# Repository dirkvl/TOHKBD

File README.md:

# TOHKBD rev2

## History

When Jolla announced their [Jolla phone](https://www.youtube.com/watch?v=tRZxM9rNyZ4) the mobile Linux community rejoiced and finally had a place to go from their N8x, N900, N950 or N9. Together with the new operating system on the inside, the OtherHalf concept was introduced. With direct data-connection into the phone it is now possible to extend the functionality on a hardware level.

Naturally, a keyboard OtherHalf was the [most requested feature](http://www.jollatides.com/2013/10/03/other-half-lets-prioritise/) by the community by far. Jolla however was still getting started and getting their phone launched with the minimum of Sailors at the time. This was left to the community to develop.

In [June 2013](http://talk.maemo.org/showthread.php?t=91535) one idiot thought he could easily make this -how hard could it be, really?- and started on his journey. After some time this foolish individual make TOHKBD-rev1: hackish, ugly, frankensteined, terrible durability and way too much work to assemble. But it worked. 

After this project ended there was a period of other Funky-TOH development, with during that time a lot of requests of making more keyboards. Little did they knew that in the background the imfamous 'dirkvl' together with his trusty 'kimmoli' were cooking up a new version. A better one. The One.

With an [open application](https://twitter.com/andrewzhilin/status/493485714798313472) on the hashweb/tweetspace Andrew joined the team and provid himself to be the missing piece of the three piece puzzle. With a complete team, a solid design and a strong backing from the rest of the community, the TOHKBD-team set out onto the open crowdfunding sea. [And struck gold.](https://www.kickstarter.com/projects/2028347278/tohkbd-the-other-half-keyboard-for-your-jolla)

## Hardware

### Electronics

#### TOH-cover

In the cover that snap onto the phone there is very little going on. There is a PCB that connects to all [6 pogo-pins](https://jolla.com/the-other-half-developer-kit/). Connecting to these pins is a [voltage regulator](https://github.com/dirkvl/TOHKBD/tree/master/Eagle/pics/MCP1703.jpg) and an EEPROM. 

This is a memory module that contains a [Vendor and Product ID](https://wiki.merproject.org/wiki/The_other_half). The phone reads this EEPROM when it connects to start the appropriate driver.

If the driver is not installed, the phone reads the [NFC tag](http://www.nfcnetstore.com/SMARTRAC+Midas+NTAG203+12x19+mm+clear+%28NFC+Forum+Type+2%29/p/121/) on the PCB and pulls the driver from the store.

With two contact pads (8mm PCBs) the keyboard piece can make contact, all 6 pins are available.

#### Keyboard piece

In the keyboard a little more is going on. The main driver is the [TCA8424](http://www.ti.com/product/TCA8424/description). It runs on 1.8V I2C lines and has three notification LEDs connected, where the TCA8424 acts as an open drain. The LEDs have some probing pads for testing during production.

This connects to the keyboard matrix. It waits untill a key is pressed, then starts scanning and notifies the phone via the INT pin that is has data to be read.

There is an additional EEMPROM in the keyboard piece, containing the keypad layout version. The A0 address pin is pulled high to make it shift one address place and not conflict with the EEPROM in the TOH-cover.

The backlight consists of 10 x 0402 LEDs, controlled with a [n-channel MOSFET](http://en.wikipedia.org/wiki/MOSFET) by the TCA8424.

The keyboard detection is done with a PNP transistor.

```
1. Phone detects TOH-cover
2. Phone launches TOHKBD driver
3. The driver shuts down the 3V3 line and starts listening to the interrupt
4. When the keyboard connects, the PNP transistor shorts the interrupt line to ground
5. The phone detects the grounding of INT and powers up de 3V3 line
6. The 3V3 disables the grounding on INT in the transistor
7. The phone probes whether the TCA8424 is present
8a. If the TCA8424 is present, the keyboard is present and working and all is set in motion
8b. If the TCA8424 is not present, something is wrong and the phone goes back to step 3
```

SMD part list:
```
TCA8424 - QFN40
CAT24C02 - DFN6
IRLML5203 - SOT-3
10K pullup/downs - 0603
10R led resistors - 0603
MCP1700 - SOT-3
0.1uF 6V capacitors - 0603
3.15V highbright leds - 0402
Pogo pins - Mill-Max 0906-0-15-20-76-14-11-0 (Mouser P/N: 575-906015)
```

### PCBs

Made in Eagle Cadsoft. The gerber files are linked below:

[Cover PCB](https://raw.githubusercontent.com/dirkvl/TOHKBD/master/Eagle/Cover.rar)

[Keyboard PCB](https://raw.githubusercontent.com/dirkvl/TOHKBD/master/Eagle/Keyboard.rar)

### SMD assembly

The first step in SMD assembly is applying solder past on the PCB with a stencil printer.

Next a pick&place machine puts the components in the right place on the PCB. I use a TM220A.

Because the accuracy of the machine it not astronomical, the allignment of every component is checked and adjusted by hand if neccessary. 

The solderpaste is melted in a reflow oven. (T-962A)

Lastly the PCB is tested manually and all shorts are corrected with a soldering iron.

### Frames

The frames are 3D printed (using a process called lasersintering) by Shapeways. If you want to change the colour of your TOHKBD, you can order one of these parts from them:

Cover link
Keyboard link

### Magnet system

The keyboard part uses magnets to attach and detach in all positions. 

The magnets used are the [D61-N52](https://www.kjmagnetics.com/proddetail.asp?prod=D61-N52) and [D62-N52](https://www.kjmagnetics.com/proddetail.asp?prod=D62-N52) from KJMagnetics.

<insert picture with dimensions>

### Keypad

Credits to Andrew

### Layouts

designs, files etc

### Backplate

<Dimensions>

## Software

[Link to Kimmoli's Github](https://github.com/kimmoli/)

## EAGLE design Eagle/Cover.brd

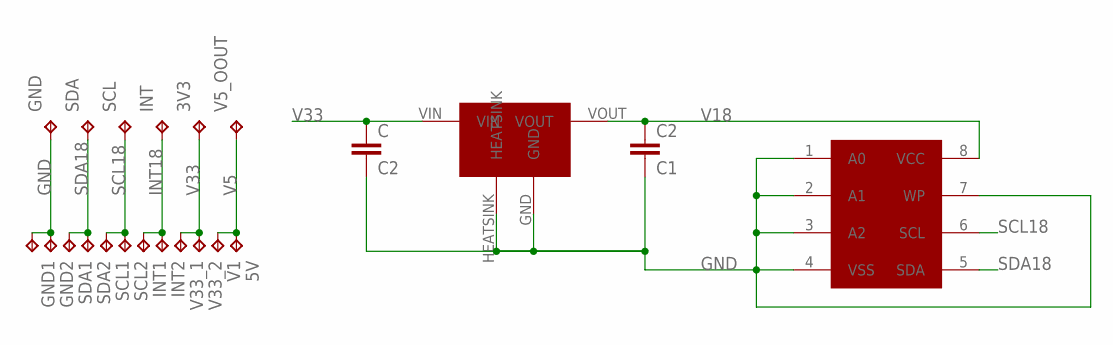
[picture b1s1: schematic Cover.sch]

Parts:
3V3: TPTP20SQ; TP20SQ
5V: V5; TP20SQ
C: C2; C0603
C2: C1; C0603
GND, GND1, GND2: TPTP20SQ; TP20SQ
INT, INT1, INT2: TPTP20SQ; TP20SQ
SCL, SCL1, SCL2: TPTP20SQ; TP20SQ
SDA: TPTP20SQ; TP20SQ
SDA1, SDA2: SDA; TP20SQ
U$1: CAT24
U$2: MCP1700-DFN6; DFN6-2X2
V1: V5; TP20SQ
V5_OOUT, V33_1, V33_2: TPTP20SQ; TP20SQ

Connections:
GND: C.2, C2.2, GND.TP, GND1.TP, GND2.TP, U$1.1 (A0), U$1.2 (A1), U$1.3 (A2), U$1.4 (VSS), U$1.7 (WP), U$2.GND, U$2.HEATSINK
INT18: INT.TP, INT1.TP, INT2.TP
SCL18: SCL.TP, SCL1.TP, SCL2.TP, U$1.6 (SCL)
SDA18: SDA.TP, SDA1.TP, SDA2.TP, U$1.5 (SDA)
V5: 5V.TP, V1.TP, V5_OOUT.TP
V18: C2.1, U$1.8 (VCC), U$2.VOUT
V33: 3V3.TP, C.1, U$2.VIN, V33_1.TP, V33_2.TP

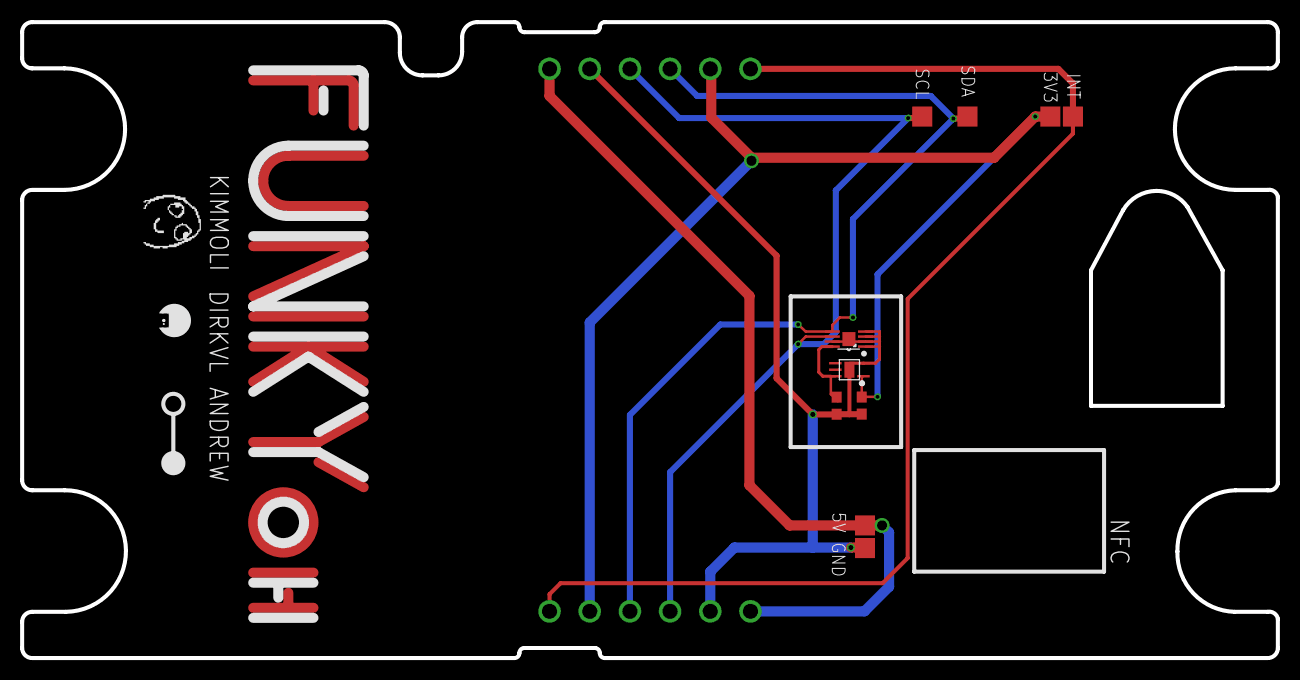
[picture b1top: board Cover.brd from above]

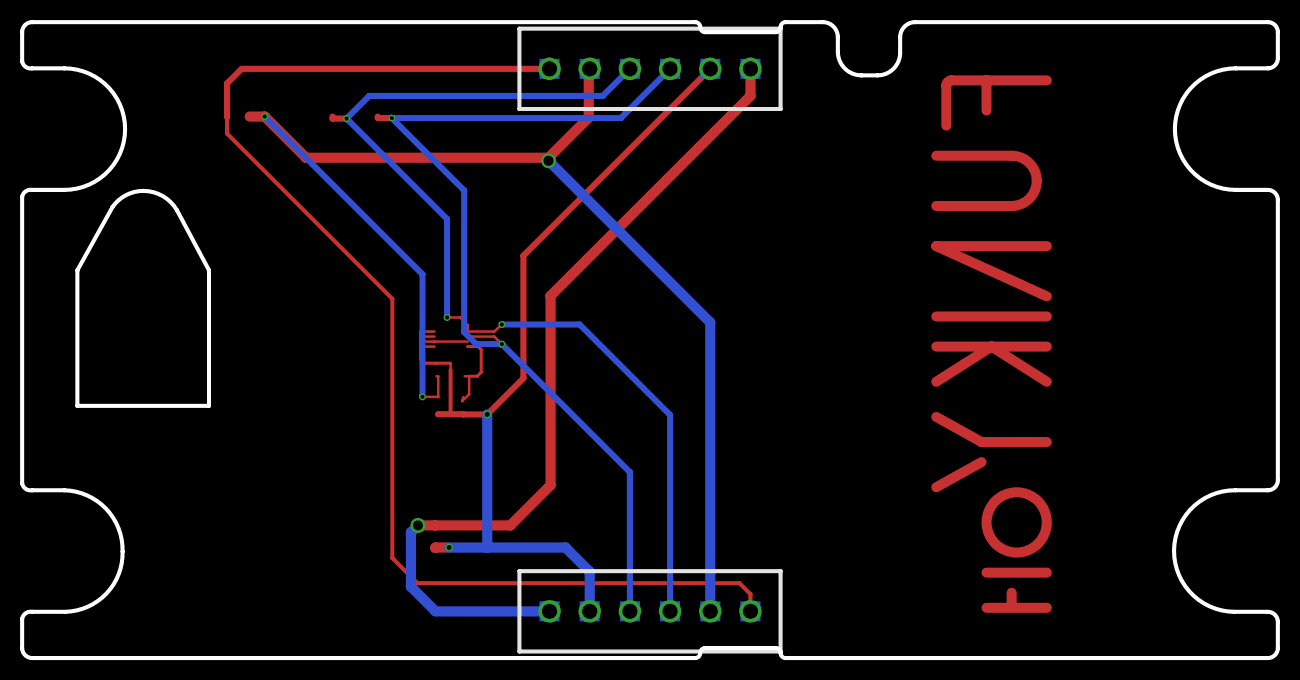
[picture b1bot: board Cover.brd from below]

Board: 2 copper layers, 125.0 x 63.3 mm, 24 parts (12 on the bottom side), 7 nets.

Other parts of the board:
U$3: FUNKY
U$4: DAFUG

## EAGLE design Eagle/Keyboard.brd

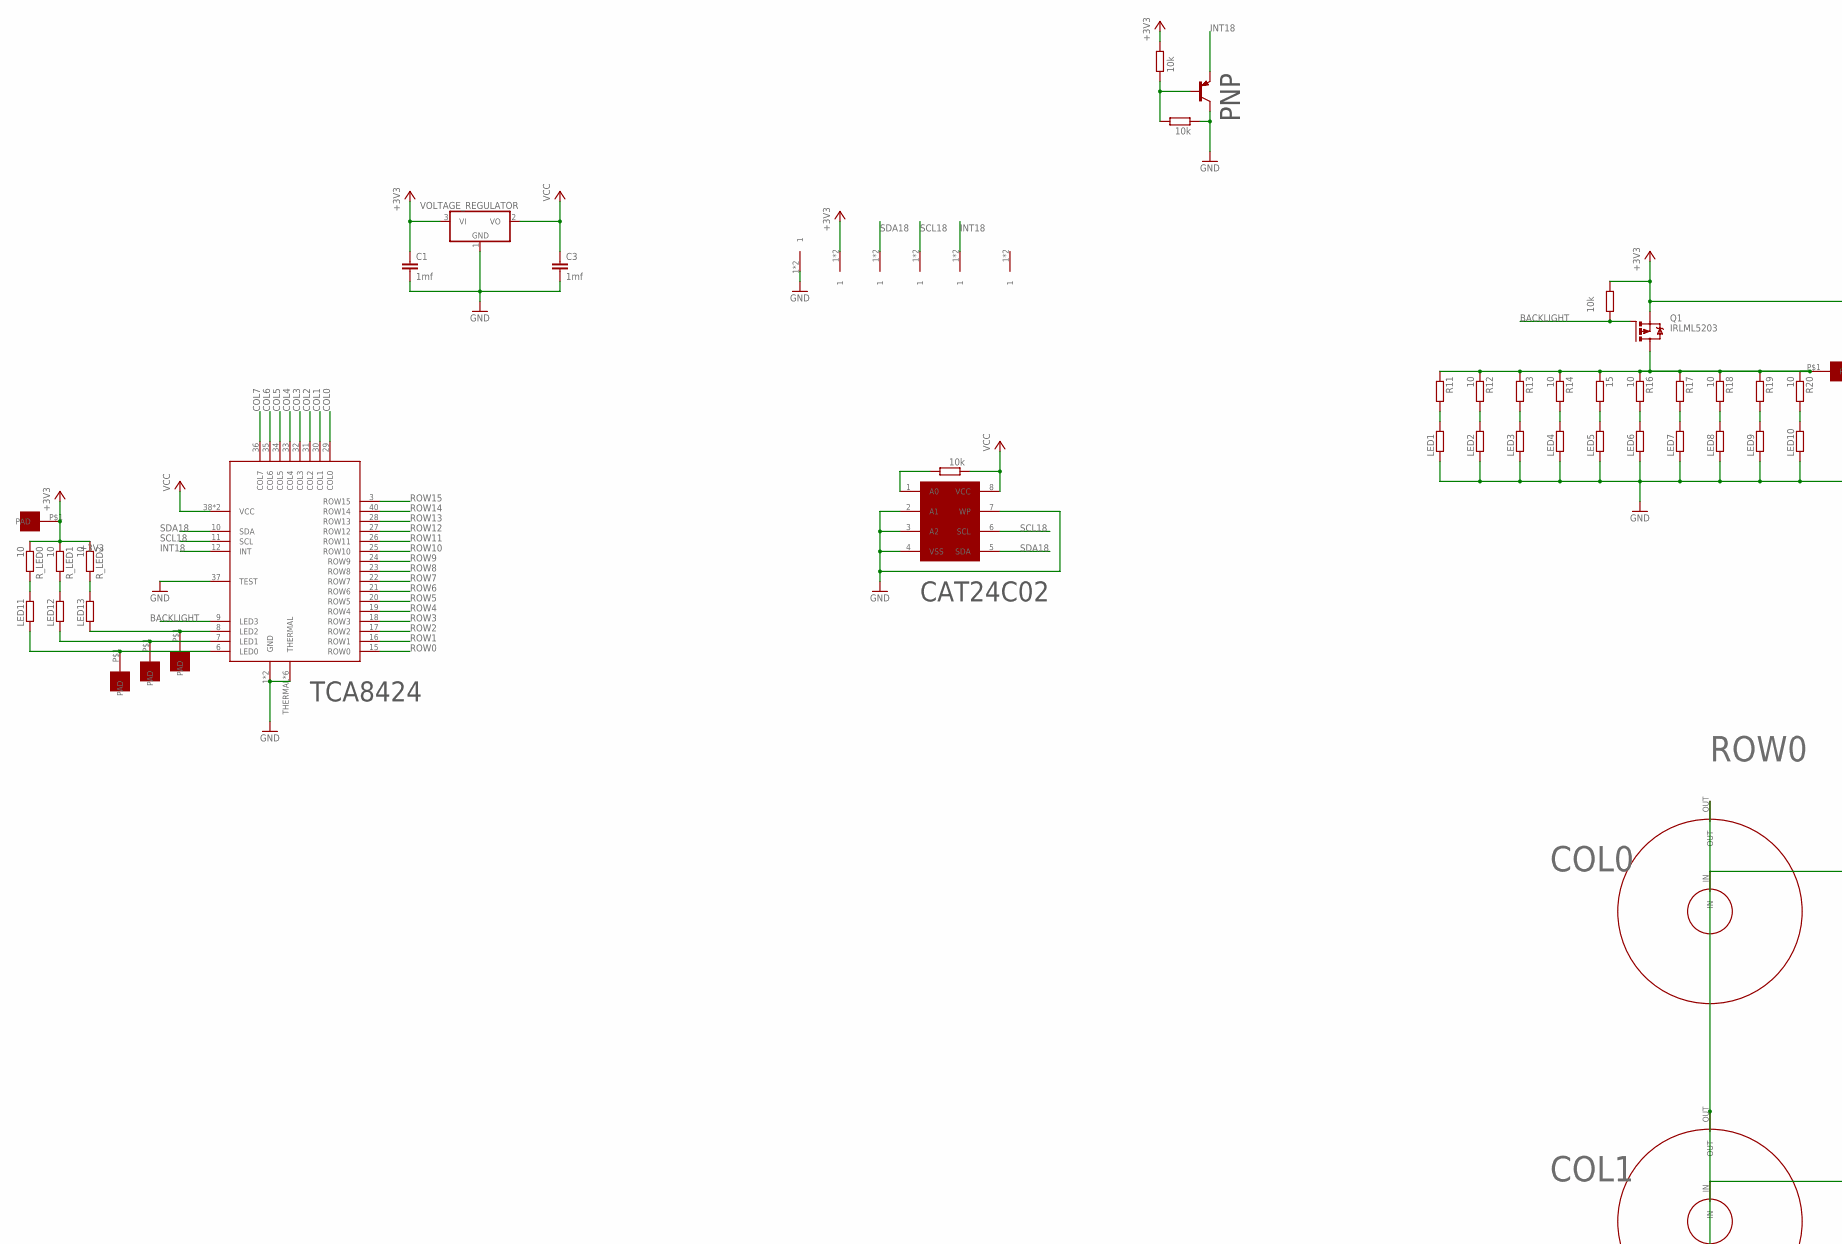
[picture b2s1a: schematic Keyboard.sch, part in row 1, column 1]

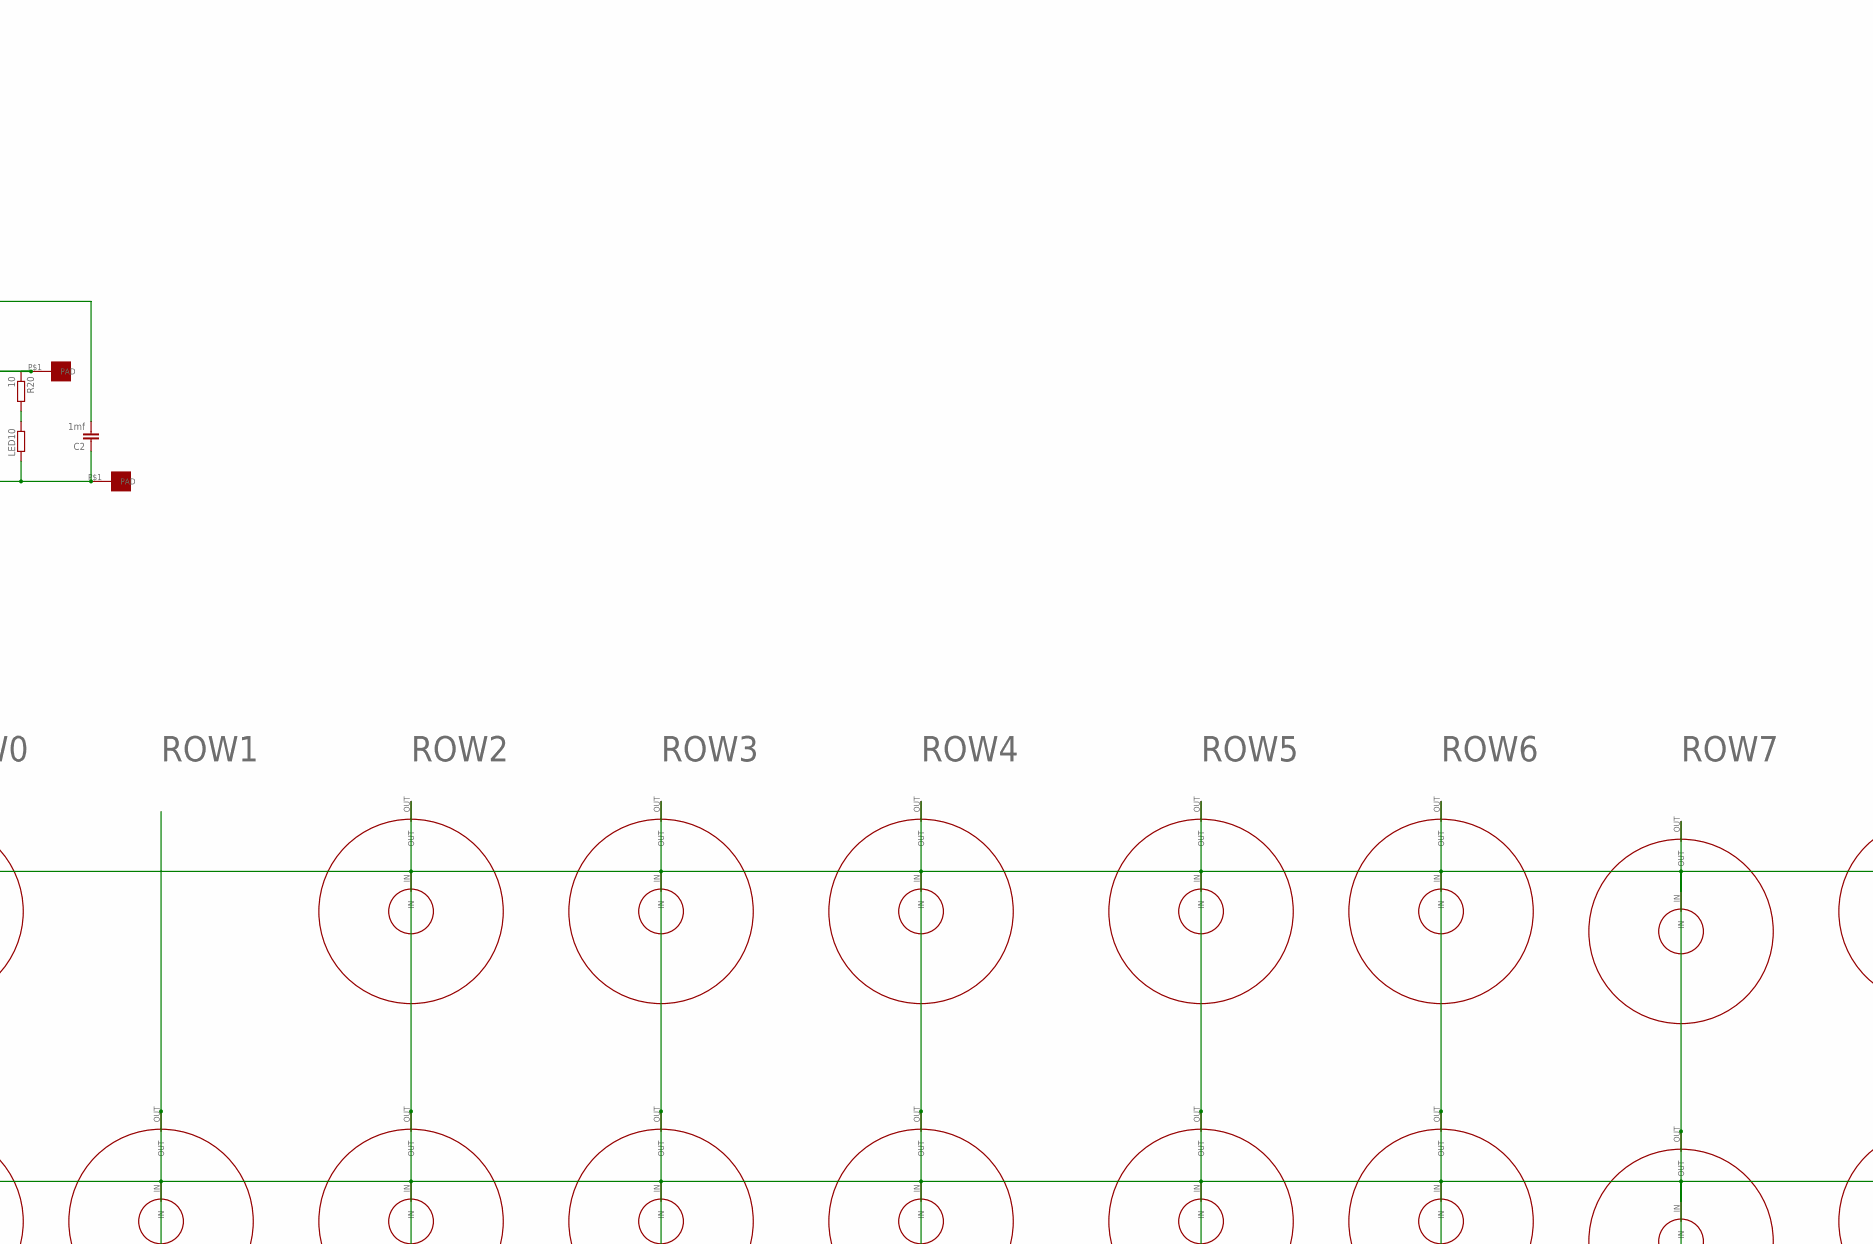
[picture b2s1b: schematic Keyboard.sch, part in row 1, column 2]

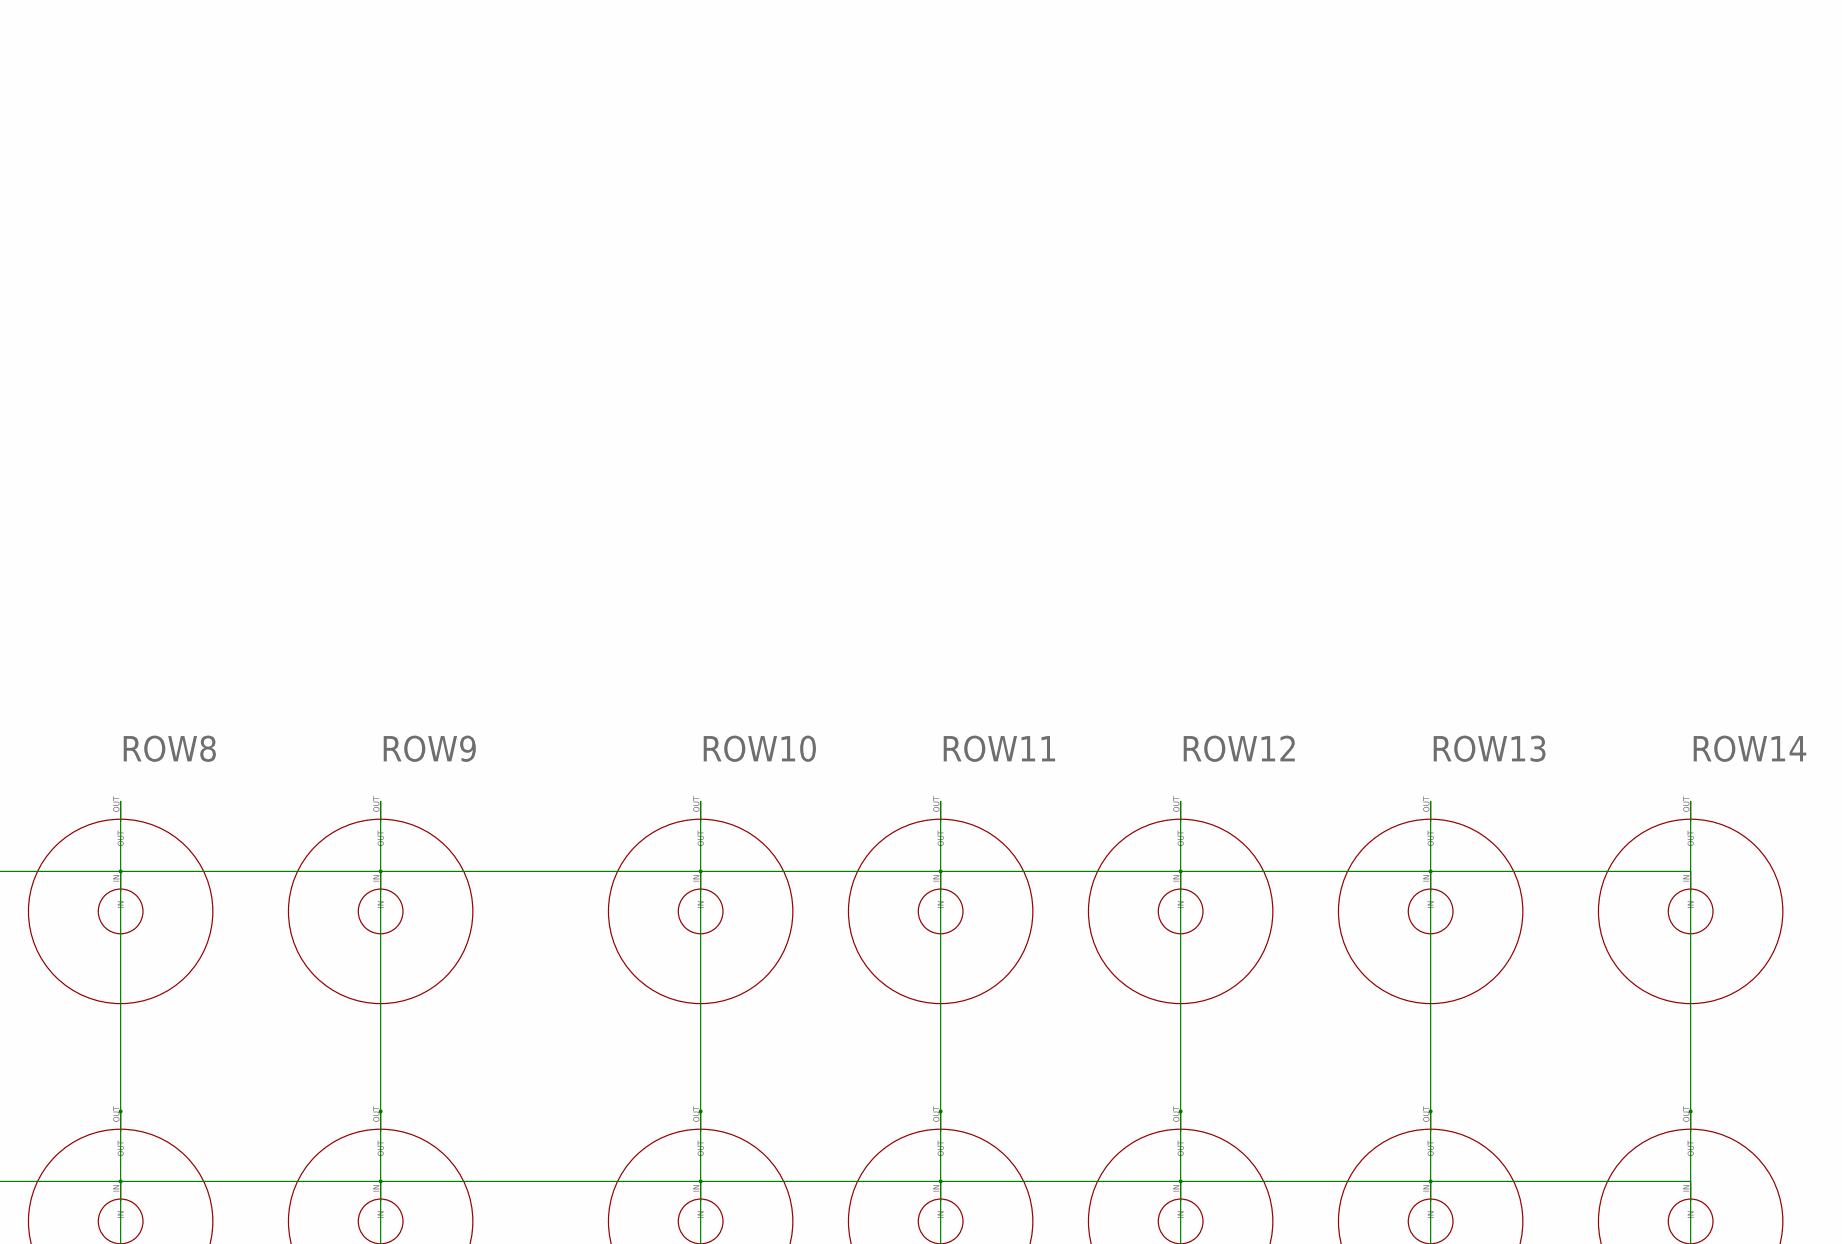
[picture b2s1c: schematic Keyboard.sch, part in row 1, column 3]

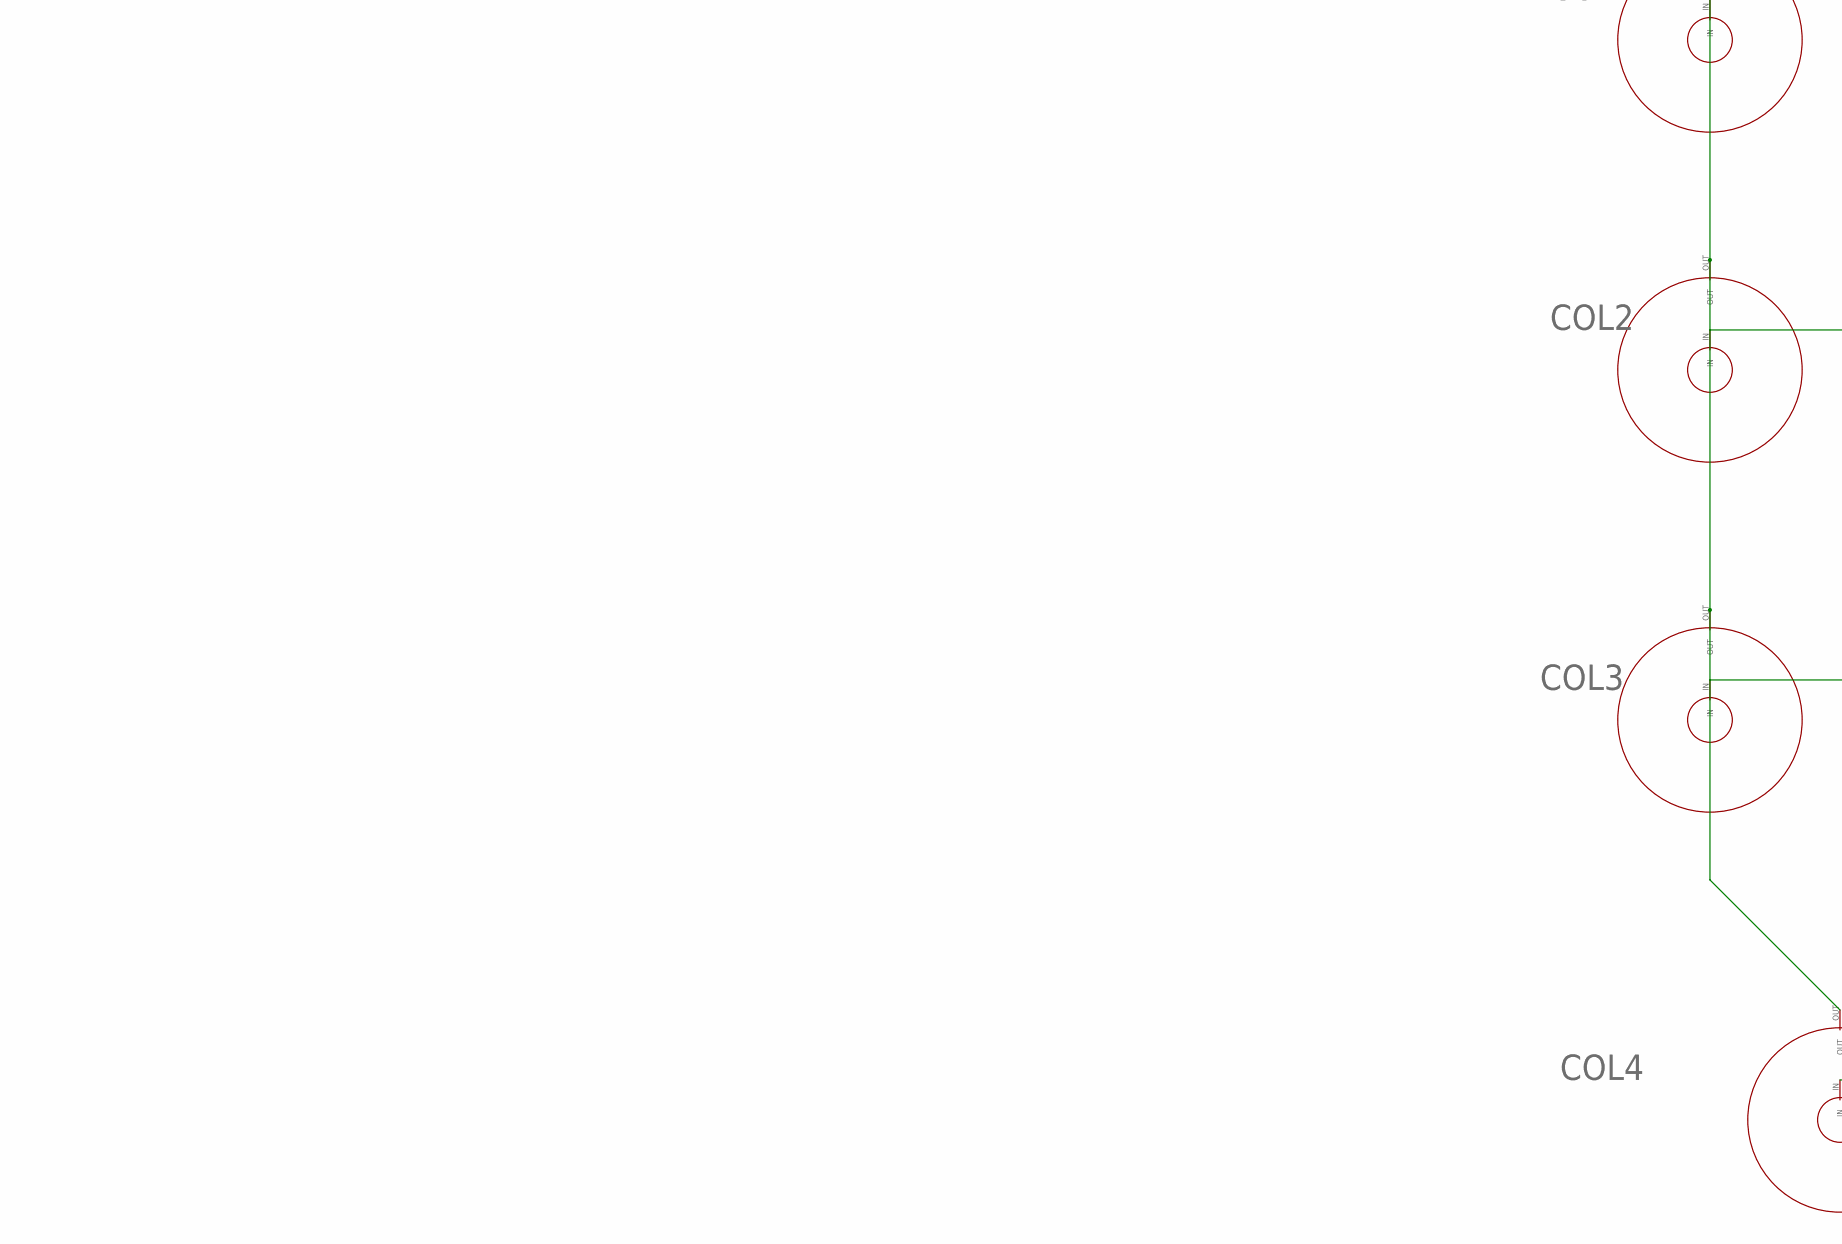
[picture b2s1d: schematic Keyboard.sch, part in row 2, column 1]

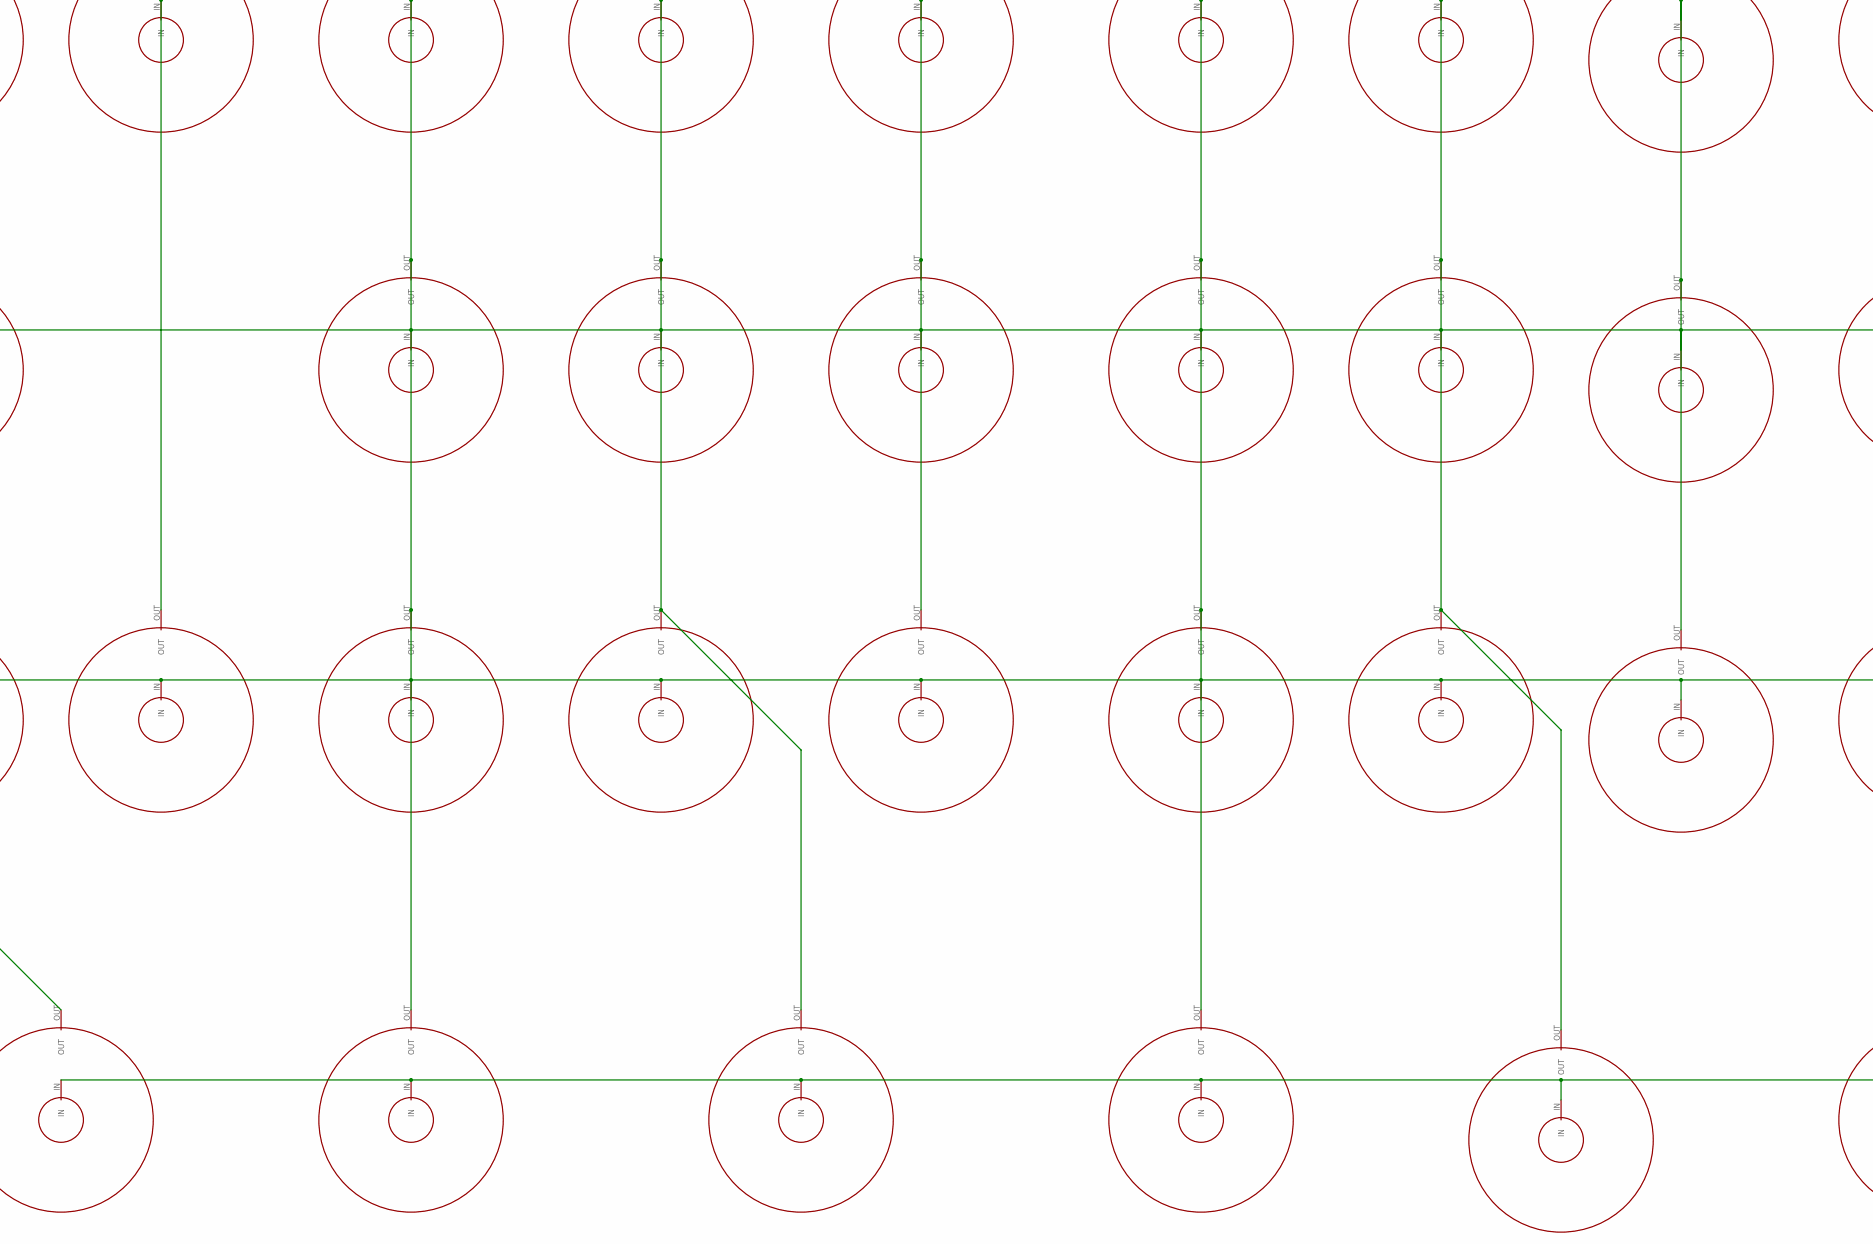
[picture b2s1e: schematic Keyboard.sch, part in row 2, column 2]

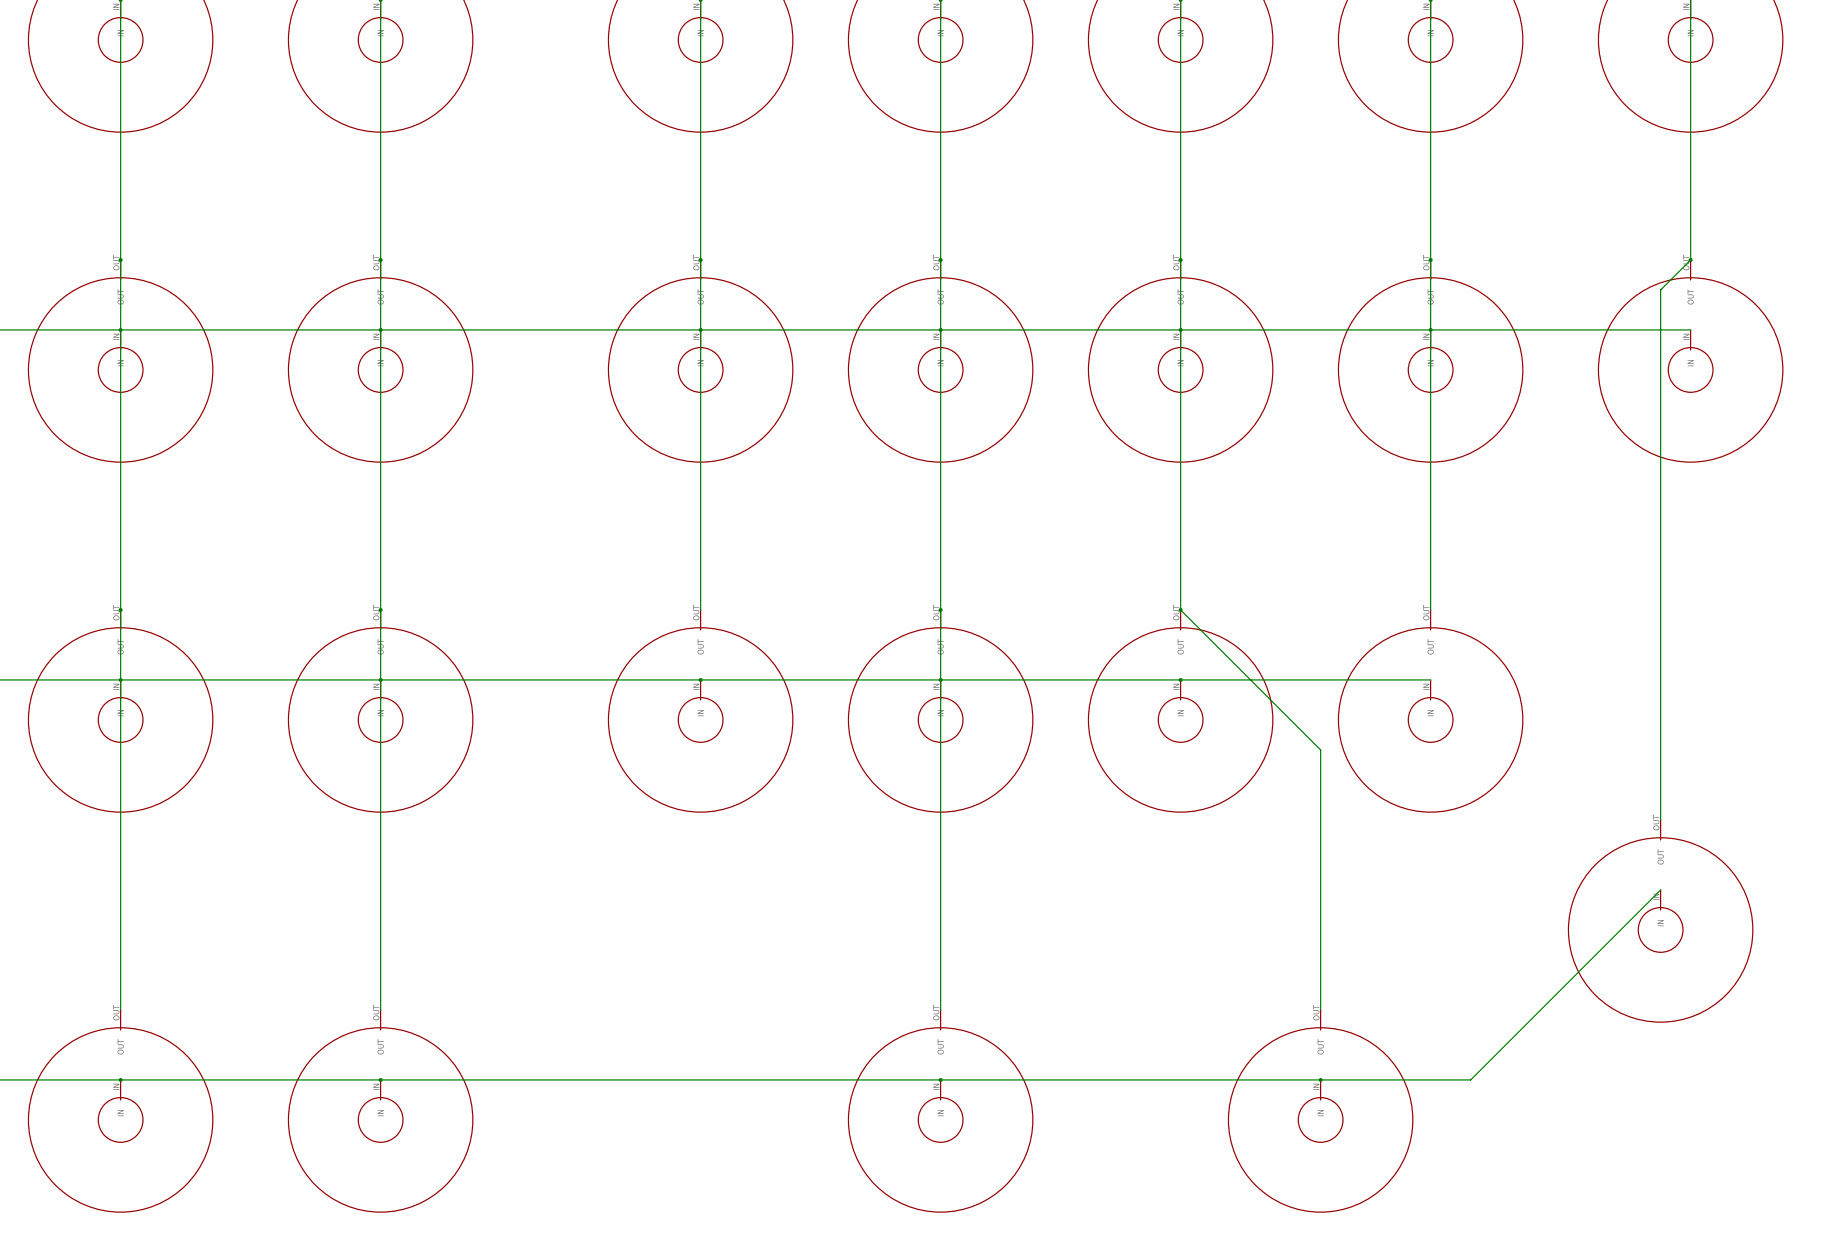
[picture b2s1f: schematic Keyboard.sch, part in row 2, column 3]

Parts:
15: R-EU_R0603; R0603
+: PAD
BL_PULLUP: 10k; R0603
C1, C2, C3: 1mf; C0603
LED1, LED2, LED3, LED4, LED5, LED6, LED7, LED8, LED9, LED10, LED11, LED12, LED13: R-EU_R0402; R0402
PNP_DOWN, PNP_DOWN1: 10k; R0603
PNP_UP: 10k; R0603
Q1: IRLML5203; MICRO3
Q2: MMBTA56-SOT23; SOT23
R11, R13, R17, R19: R-EU_R0603; R0603
R12, R14, R16, R18, R20: 10; R0603
R_LED0, R_LED1, R_LED2: 10; R0603
U$1: CAT24
U$2: TCA8424; QFN40
U$3, U$4, U$5, U$6, U$7, U$8: BOTTOM_POGO; POGO
U$9, U$11, U$12, U$13, U$14, U$15, U$16, U$17, U$18, U$19, U$20, U$21, U$22, U$23, U$24, U$25, U$26, U$27, U$28, U$29, U$30, U$31, U$32, U$33, U$34, U$35, U$36, U$37, U$38, U$39, U$40, U$41, U$42, U$43, U$44, U$45, U$46, U$47, U$48, U$49, U$50, U$51, U$52, U$54, U$55, U$56, U$57, U$58, U$59, U$60, U$61, U$62, U$63, U$64, U$65, U$66, U$67, U$68, U$69, U$70, U$72, U$73, U$75, U$76, U$77, U$79, U$81: DOME; 4MM
U$53, U$71, U$74, U$78, U$80: PAD
VOLTAGE_REGULATOR: SOT23

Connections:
+3V3: +.P$1, BL_PULLUP.1, C1.1, C2.2, PNP_UP.1, Q1.2 (S), R_LED0.1, R_LED1.1, R_LED2.1, U$4.1, U$4.P$2, VOLTAGE_REGULATOR.3 (VI)
BACKLIGHT: BL_PULLUP.2, Q1.1 (G), U$2.9 (LED3)
COL0: U$2.29 (COL0), U$9.IN, U$11.IN, U$12.IN, U$13.IN, U$14.IN, U$15.IN, U$16.IN, U$17.IN, U$18.IN, U$19.IN, U$20.IN, U$21.IN, U$22.IN, U$23.IN
COL1: U$2.30 (COL1), U$24.IN, U$25.IN, U$26.IN, U$27.IN, U$28.IN, U$29.IN, U$30.IN, U$31.IN, U$32.IN, U$33.IN, U$34.IN, U$35.IN, U$36.IN, U$37.IN, U$38.IN
COL2: U$2.31 (COL2), U$39.IN, U$40.IN, U$41.IN, U$42.IN, U$43.IN, U$44.IN, U$45.IN, U$46.IN, U$47.IN, U$48.IN, U$49.IN, U$50.IN, U$51.IN, U$52.IN
COL3: U$2.32 (COL3), U$54.IN, U$55.IN, U$56.IN, U$57.IN, U$58.IN, U$59.IN, U$60.IN, U$61.IN, U$62.IN, U$63.IN, U$64.IN, U$65.IN, U$66.IN, U$68.IN
COL4: U$2.33 (COL4), U$67.IN, U$69.IN, U$70.IN, U$72.IN, U$73.IN, U$75.IN, U$76.IN, U$77.IN, U$79.IN, U$81.IN
COL5: U$2.34 (COL5)
COL6: U$2.35 (COL6)
COL7: U$2.36 (COL7)
DRAIN: 15.1, Q1.3 (D), R11.1, R12.1, R13.1, R14.1, R16.1, R17.1, R18.1, R19.1, R20.1, U$78.P$1
GND: C1.2, C2.1, C3.2, LED1.1, LED2.1, LED3.1, LED4.1, LED5.1, LED6.1, LED7.1, LED8.1, LED9.1, LED10.1, PNP_DOWN.2, Q2.3 (C), U$1.2 (A1), U$1.3 (A2), U$1.4 (VSS), U$1.7 (WP), U$2.1 (GND), U$2.4 (GND), U$2.37 (TEST), U$2.THERMAL, U$2.VIA1 (THERMAL), U$2.VIA2 (THERMAL), U$2.VIA3 (THERMAL), U$2.VIA4 (THERMAL), U$2.VIA5 (THERMAL), U$3.1, U$3.P$2, U$80.P$1, VOLTAGE_REGULATOR.1 (GND)
INT18: Q2.2 (E), U$2.12 (INT), U$7.1, U$7.P$2
LED_GROUND0: LED11.2, R_LED0.2
LED_GROUND1: LED12.2, R_LED1.2
LED_GROUND2: LED13.2, R_LED2.2
unnamed: LED1.2, R11.2
unnamed: LED2.2, R12.2
unnamed: LED3.2, R13.2
unnamed: LED4.2, R14.2
unnamed: 15.2, LED5.2
unnamed: LED6.2, R16.2
unnamed: LED7.2, R17.2
unnamed: LED8.2, R18.2
unnamed: LED9.2, R19.2
unnamed: LED10.2, R20.2
unnamed: PNP_DOWN.1, PNP_UP.2, Q2.1 (B)
unnamed: LED12.1, U$2.7 (LED1), U$71.P$1
unnamed: LED11.1, U$2.6 (LED0), U$53.P$1
unnamed: LED13.1, U$2.8 (LED2), U$74.P$1
unnamed: PNP_DOWN1.2, U$1.1 (A0)
ROW0: U$2.15 (ROW0), U$9.OUT, U$24.OUT, U$39.OUT, U$54.OUT, U$69.OUT
ROW1: U$2.16 (ROW1), U$38.OUT, U$68.OUT
ROW2: U$2.17 (ROW2), U$11.OUT, U$25.OUT, U$40.OUT, U$55.OUT, U$70.OUT
ROW3: U$2.18 (ROW3), U$12.OUT, U$26.OUT, U$41.OUT, U$56.OUT, U$72.OUT
ROW4: U$2.19 (ROW4), U$13.OUT, U$27.OUT, U$42.OUT, U$57.OUT
ROW5: U$2.20 (ROW5), U$14.OUT, U$28.OUT, U$43.OUT, U$58.OUT, U$73.OUT
ROW6: U$2.21 (ROW6), U$15.OUT, U$29.OUT, U$44.OUT, U$59.OUT, U$75.OUT
ROW7: U$2.22 (ROW7), U$16.OUT, U$30.OUT, U$45.OUT, U$60.OUT
ROW8: U$2.23 (ROW8), U$17.OUT, U$31.OUT, U$46.OUT, U$61.OUT, U$76.OUT
ROW9: U$2.24 (ROW9), U$18.OUT, U$32.OUT, U$47.OUT, U$62.OUT, U$77.OUT
ROW10: U$2.25 (ROW10), U$19.OUT, U$33.OUT, U$48.OUT, U$63.OUT
ROW11: U$2.26 (ROW11), U$20.OUT, U$34.OUT, U$49.OUT, U$64.OUT, U$79.OUT
ROW12: U$2.27 (ROW12), U$21.OUT, U$35.OUT, U$50.OUT, U$65.OUT, U$81.OUT
ROW13: U$2.28 (ROW13), U$22.OUT, U$36.OUT, U$51.OUT, U$66.OUT
ROW14: U$2.40 (ROW14), U$23.OUT, U$37.OUT, U$52.OUT, U$67.OUT
ROW15: U$2.3 (ROW15)
SCL18: U$1.6 (SCL), U$2.11 (SCL), U$6.1, U$6.P$2
SDA18: U$1.5 (SDA), U$2.10 (SDA), U$5.1, U$5.P$2
VCC: C3.1, PNP_DOWN1.1, U$1.8 (VCC), U$2.38 (VCC), U$2.39 (VCC), VOLTAGE_REGULATOR.2 (VO)

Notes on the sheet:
TCA8424
CAT24C02
PNP

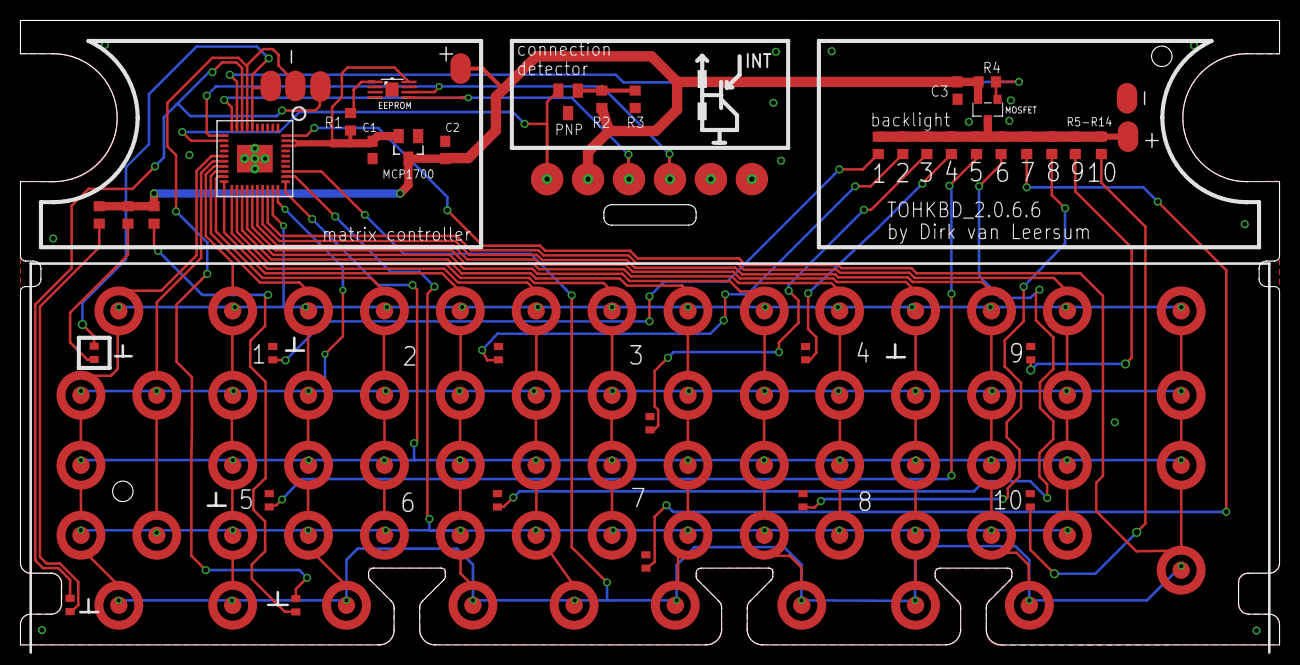
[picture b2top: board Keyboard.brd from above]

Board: 2 copper layers, 123.0 x 61.0 mm, 117 parts (0 on the bottom side), 46 nets.

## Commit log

2015-02-21 :boom::camel: Added .gitattributes & .gitignore files
2015-02-21 CAD files
2015-03-08 pictures of bottom schematic
2015-03-12 History and some electronics details
2015-03-12 pics dont work
2015-03-12 pics should work now
2015-03-15 some more info
2015-03-17 Added FDM printer compatible models
2015-03-17 added model for the bumps that go agains the alignment cavities in the KBD casing
2015-04-05 Eagle files
2015-04-05 eagle documentation
2015-04-05 typo
2015-04-05 cleaning up
2015-06-06 pics and info
2015-06-06 moar info
2015-06-06 troubles
2015-10-07 Add pogo pin part number to SMD part list
